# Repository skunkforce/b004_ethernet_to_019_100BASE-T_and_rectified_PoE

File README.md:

# edgy_board number b004
This design is part of the [edgy board project](https://github.com/skunkforce/edgy_boards). It provides an RJ45 100BASE-T connector with PoE rectifier.

# getting started
This repository uses submodules. After cloning use the command 

```$ git submodule update --init --recursive```

to pull the submodules before opening the project with kicad. 

# Tests
Tests can be found in [TESTS.md](TESTS.md)

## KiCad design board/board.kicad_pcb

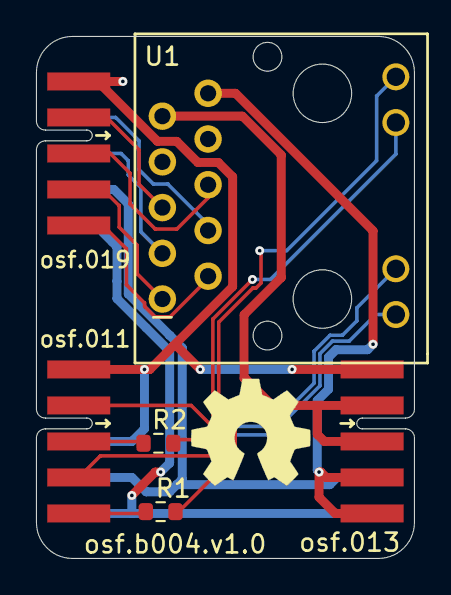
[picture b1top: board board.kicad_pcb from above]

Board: 2 copper layers, 21.0 x 29.0 mm, 7 parts (0 on the bottom side), 17 nets.

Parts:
J1: 019_100BASE-T_2x5; on_edge_2x05_device
J2: 011_GPIO; on_edge_2x05_device
J3: PoE; on_edge_2x05_host
LOGO1: Logo_Open_Hardware_Small; OSHW-Symbol_6.7x6mm_SilkScreen
R1, R2: 330R; R_0603_1608Metric
U1: 7499211121A

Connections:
/PoE_GND: J3.4 (PoE_GND), J3.5 (PoE_GND), U1.10 (VC1-)
/eth_conn/LED1+: J2.2 (GPIO0), U1.11 (LED1+)
/eth_conn/LED1-: J2.3 (GPIO1), R2.2
/eth_conn/LED2+: J2.4 (GPIO2), U1.13 (LED2+)
/eth_conn/LED2-: J2.5 (GPIO3), R1.2
/eth_conn/RCT: J1.8 (CT2), U1.3 (RCT)
/eth_conn/RD+: J1.4 (TD2+), U1.1 (RD+)
/eth_conn/RD-: J1.5 (TD2-), U1.2 (RD-)
/eth_conn/TCT: J1.7 (CT1), U1.4 (TCT)
/eth_conn/TD+: J1.2 (TD1+), U1.5 (TD+)
/eth_conn/TD-: J1.3 (TD1-), U1.6 (TD-)
/eth_conn/VC1+: J3.2 (48V), J3.3 (48V), U1.9 (VC1+)
GND: J1.1 (GND), J1.6 (GND), J2.1 (GND), J2.8 (GND), J3.1 (GND)
unnamed: J1.9 (3.3V), J2.9 (3.3V), J3.9 (3.3V)
unnamed: J1.10 (5V), J2.10 (5V), J3.10 (5V)
unnamed: R1.1, U1.14 (LED2)
unnamed: R2.1, U1.12 (LED1)

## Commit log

2023-02-22 initial
2023-03-01 updated put_on_edge submodule
2023-03-04 modernized to new put_on_edge connectors with 3.3 and 5v
